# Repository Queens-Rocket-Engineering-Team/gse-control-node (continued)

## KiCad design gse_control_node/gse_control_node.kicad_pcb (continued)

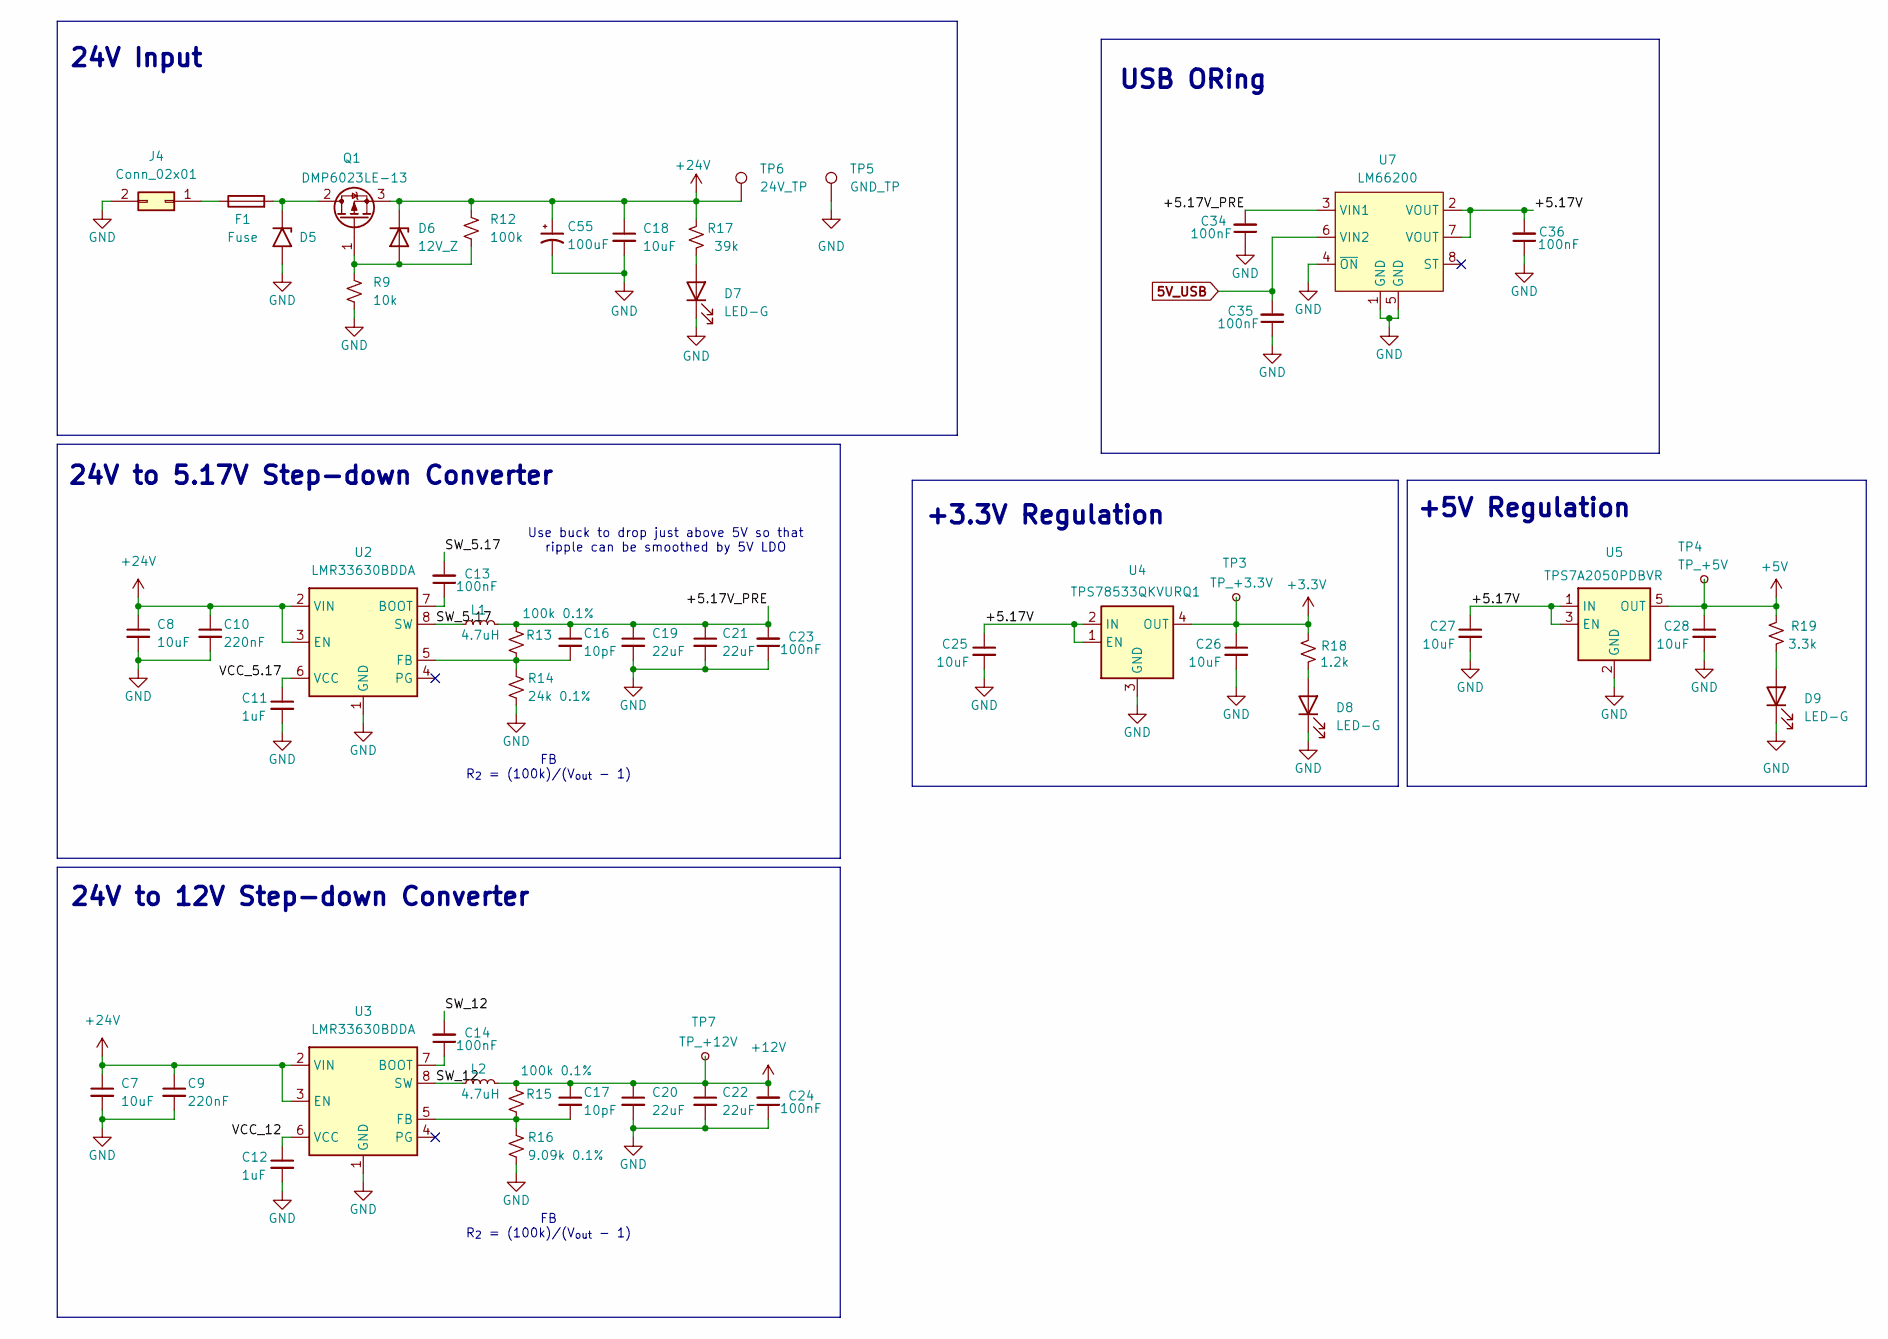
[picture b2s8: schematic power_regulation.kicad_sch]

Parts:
C7, C8, C18: 10uF; C_1206_3216Metric; LCSC C13585
C9, C10: 220nF; C_0805_2012Metric; LCSC C5378
C11, C12: 1uF; C_0603_1608Metric; LCSC C15849
C13, C14, C23, C24, C34, C35, C36: 100nF; C_0402_1005Metric; LCSC C307331
C16, C17: 10pF; C_0603_1608Metric; LCSC C1634
C19, C20, C21, C22: 22uF; C_0805_2012Metric; LCSC C45783
C25, C26, C27, C28: 10uF; C_0805_2012Metric; LCSC C15850
C55: 100uF; CP_Radial_D8.0mm_P5.00mm; MPN EEU-FR1H101B
D5: SMCJ26A-13-F; D_SMC; LCSC C135156
D6: 12V_Z; D_SOD-123; LCSC C500776
D7, D8, D9: LED-G; LED_0805_2012Metric; LCSC C2297
F1: Fuse; Fuseholder_Blade_Mini_Keystone_3568; LCSC N/A
J4: Conn_02x01; Molex_Mini-Fit_Jr_5566-02A_2x01_P4.20mm_Vertical; LCSC N/A
L1, L2: 4.7uH; L_Bourns_SRP7028A_7.3x6.6mm; LCSC C840529
Q1: DMP6023LE-13; SOT-223-3_TabPin2; LCSC C154901
R9: 10k; R_0603_1608Metric; LCSC C25804
R12: 100k; R_0603_1608Metric; LCSC C122538
R13, R15: 100k 0.1%; R_0603_1608Metric; LCSC C122538
R14: 24k 0.1%; R_0603_1608Metric; LCSC C326729
R16: 9.09k 0.1%; R_0603_1608Metric; LCSC C861611
R17: 39k; R_0603_1608Metric; LCSC C23153
R18: 1.2k; R_0603_1608Metric
R19: 3.3k; R_0603_1608Metric; LCSC C22978
TP3: TP_+3.3V; TestPoint_Pad_D1.0mm; LCSC N/A
TP4: TP_+5V; TestPoint_Pad_D1.0mm; LCSC N/A
TP5: GND_TP; TestPoint_Loop_D2.50mm_Drill1.0mm; LCSC N/A
TP6: 24V_TP; TestPoint_Loop_D2.50mm_Drill1.0mm; LCSC N/A
TP7: TP_+12V; TestPoint_Pad_D1.0mm; LCSC N/A
U2, U3: LMR33630BDDA; Texas_HSOP-8-1EP_3.9x4.9mm_P1.27mm_ThermalVias; LCSC C544370
U4: TPS78533QKVURQ1; TO-252-4; LCSC C3748131
U5: TPS7A2050PDBVR; SOT-23-5; LCSC C2864504
U7: LM66200; SOT-583-8; LCSC C3235556

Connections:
5V_USB: C35.2, U7.6 (VIN2); also elsewhere on the board
+3.3V: C26.1, R18.2, TP3.1 (1_1), U4.4 (OUT); also elsewhere on the board
+5V: C28.1, R19.2, TP4.1 (1_1), U5.5 (OUT); also elsewhere on the board
+12V: C17.1, C20.1, C22.1, C24.2, L2.2, R15.1, TP7.1 (1_1); also elsewhere on the board
+24V: C7.1, C8.1, C9.1, C10.1, C18.1, C55.1, D6.1 (K), Q1.3 (S), R12.1, R17.2, TP6.1 (1_1), U2.2 (VIN), U2.3 (EN), U3.2 (VIN), U3.3 (EN); also elsewhere on the board
/Power Regulation/+5.17V: C25.1, C27.1, C36.2, U4.1 (EN), U4.2 (IN), U5.1 (IN), U5.3 (EN), U7.2 (VOUT), U7.7 (VOUT)
/Power Regulation/+5.17V_PRE: C16.1, C19.1, C21.1, C23.2, C34.2, L1.2, R13.1, U7.3 (VIN1)
/Power Regulation/SW_5.17: C13.2, L1.1, U2.8 (SW)
/Power Regulation/SW_12: C14.2, L2.1, U3.8 (SW)
/Power Regulation/VCC_5.17: C11.1, U2.6 (VCC)
/Power Regulation/VCC_12: C12.1, U3.6 (VCC)
GND: C7.2, C8.2, C9.2, C10.2, C11.2, C12.2, C18.2, C19.2, C20.2, C21.2, C22.2, C23.1, C24.1, C25.2, C26.2, C27.2, C28.2, C34.1, C35.1, C36.1, C55.2, D5.2 (A2), D7.1 (K), D8.1 (K), D9.1 (K), J4.2, R9.2, R14.2, R16.2, TP5.1 (1_1), U2.1 (GND), U2.9 (GND), U3.1 (GND), U3.9 (GND), U4.3 (GND), U5.2 (GND), U7.1 (GND), U7.4 (~ON), U7.5 (GND); also elsewhere on the board
unnamed: D5.1 (A1), F1.2, Q1.2 (D)
unnamed: D6.2 (A), Q1.1 (G), R9.1, R12.2
unnamed: D7.2 (A), R17.1
unnamed: D8.2 (A), R18.1
unnamed: D9.2 (A), R19.1
unnamed: F1.1, J4.1
unnamed: C13.1, U2.7 (BOOT)
unnamed: C16.2, R13.2, R14.1, U2.5 (FB)
unnamed: C14.1, U3.7 (BOOT)
unnamed: C17.2, R15.2, R16.1, U3.5 (FB)

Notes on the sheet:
Use buck to drop just above 5V so that ripple can be smoothed by 5V LDO
24V Input
24V to 5.17V Step-down Converter
FB R_{2} = (100k)/(V_{out} - 1)
24V to 12V Step-down Converter
+3.3V Regulation
USB ORing
+5V Regulation

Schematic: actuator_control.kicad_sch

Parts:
D11, D15, D19, D23: SK44BL; D_SMB; LCSC C151740
J7, J15, J22, J26: Conn_01x02; Molex_Micro-Fit_3.0_43650-0215_1x02_P3.00mm_Vertical; LCSC N/A
Q2, Q7, Q13, Q17: BSS138; SOT-23-3; LCSC C82045
R24, R36, R58, R66: 100; R_0603_1608Metric
R25, R33, R57, R65: 100k; R_0603_1608Metric; LCSC C122538

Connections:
+24V: D11.1 (K), D15.1 (K), D19.1 (K), D23.1 (K), J7.1, J15.1, J22.1, J26.1; also elsewhere on the board
ACT1_CTL: R24.1, R25.1; also elsewhere on the board
ACT2_CTL: R33.1, R36.1; also elsewhere on the board
ACT3_CTL: R57.1, R58.1; also elsewhere on the board
ACT4_CTL: R65.1, R66.1; also elsewhere on the board
GND: Q2.2 (S), Q7.2 (S), Q13.2 (S), Q17.2 (S), R25.2, R33.2, R57.2, R65.2; also elsewhere on the board
unnamed: D11.2 (A), J7.2, Q2.3 (D)
unnamed: D15.2 (A), J15.2, Q7.3 (D)
unnamed: D19.2 (A), J22.2, Q13.3 (D)
unnamed: D23.2 (A), J26.2, Q17.3 (D)
unnamed: Q2.1 (G), R24.2
unnamed: Q7.1 (G), R36.2
unnamed: Q13.1 (G), R58.2
unnamed: Q17.1 (G), R66.2

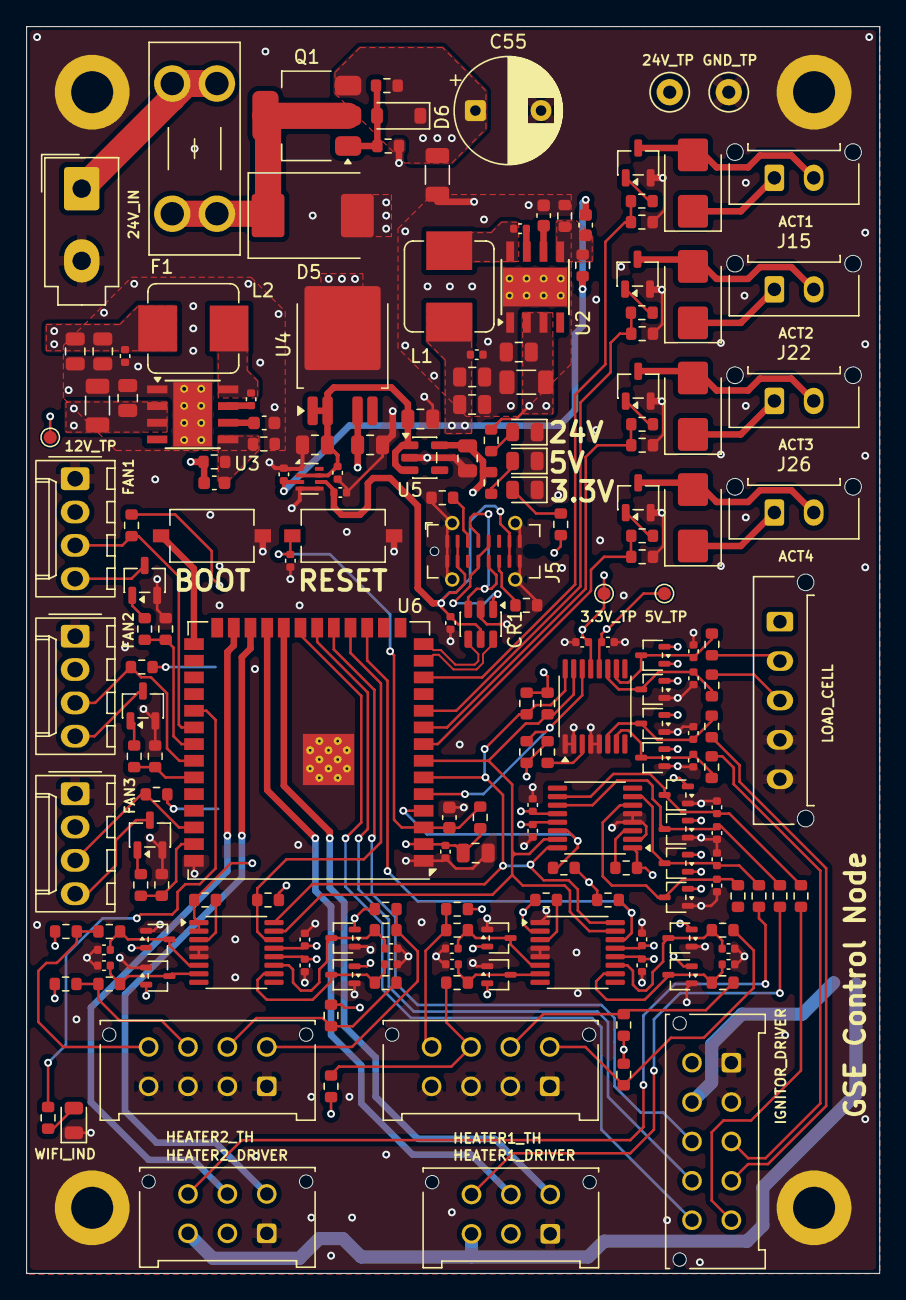
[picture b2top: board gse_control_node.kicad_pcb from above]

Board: 4 copper layers, 65.0 x 95.0 mm, 192 parts (0 on the bottom side), 104 nets.

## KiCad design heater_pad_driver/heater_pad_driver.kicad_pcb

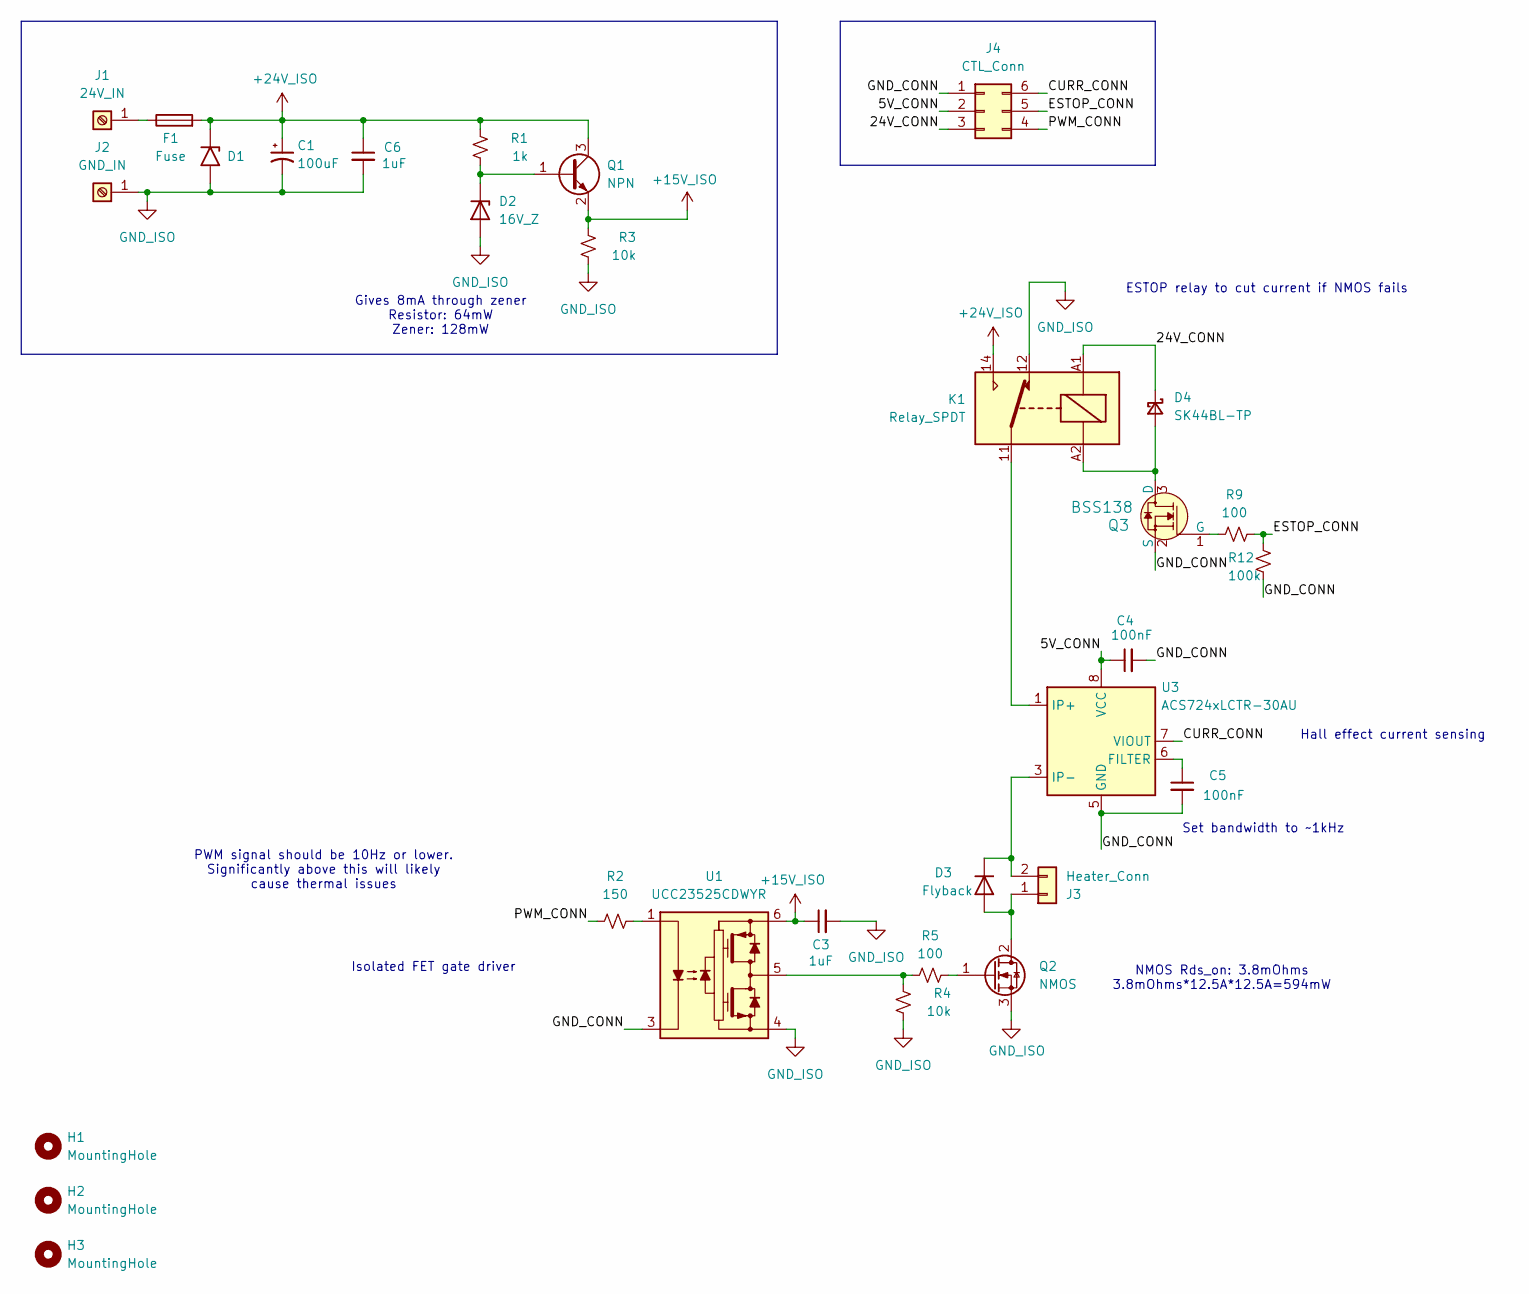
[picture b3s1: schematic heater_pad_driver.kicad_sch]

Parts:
C1: 100uF; CP_Radial_D8.0mm_P5.00mm; MPN EEU-FR1H101B
C3, C6: 1uF; C_0805_2012Metric_Pad1.18x1.45mm_HandSolder
C4, C5: 100nF; C_0805_2012Metric_Pad1.18x1.45mm_HandSolder
D1: SMCJ26A-13-F; D_SMC
D2: 16V_Z; D_SOD-123; MPN MMSZ5246BT1G
D3: Flyback; TO-220F-2_Vertical; MPN SDURK20Q60
D4: SK44BL-TP; D_SMB_Handsoldering; MPN SK44BL-TP
F1: Fuse; Fuseholder_Blade_Mini_Keystone_3568
H1, H2, H3: MountingHole; MountingHole_3.2mm_M3
J1: 24V_IN; AMT0440007DB0000G; MPN AMT0440007DB0000G
J2: GND_IN; AMT0440007DB0000G; MPN AMT0440007DB0000G
J3: Heater_Conn; AMASS_XT60PW-M_1x02_P7.20mm_Horizontal
J4: CTL_Conn; Molex_Micro-Fit_3.0_43045-0612_2x03_P3.00mm_Vertical
K1: Relay_SPDT; AZ576-1C
Q1: NPN; SOT-23_Handsoldering; MPN MMBTA06LT1G
Q2: NMOS; TO-252-2; MPN DMTH6004SK3Q-13
Q3: BSS138; SOT-23; MPN BSS138
R1: 1k; R_0805_2012Metric_Pad1.20x1.40mm_HandSolder
R2: 150; R_0805_2012Metric_Pad1.20x1.40mm_HandSolder
R3, R4: 10k; R_0805_2012Metric_Pad1.20x1.40mm_HandSolder
R5, R9: 100; R_0805_2012Metric_Pad1.20x1.40mm_HandSolder
R12: 100k; R_0805_2012Metric_Pad1.20x1.40mm_HandSolder
U1: UCC23525CDWYR; SSO-6_6.8x4.6mm_P1.27mm_Clearance8mm
U3: ACS724xLCTR-30AU; SOIC-8_3.9x4.9mm_P1.27mm; MPN ACS724LLCTR-30AU-T

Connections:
+15V_ISO: C3.1, Q1.2 (E), R3.2, U1.6 (VCC)
+24V_ISO: C1.1, C6.1, D1.1 (A1), F1.2, K1.14, Q1.3 (C), R1.2
/5V_CONN: C4.1, J4.2, U3.8 (VCC)
/24V_CONN: D4.1 (K), J4.3, K1.A1
/CURR_CONN: J4.6, U3.7 (VIOUT)
/ESTOP_CONN: J4.5, R9.2, R12.1
/GND_CONN: C4.2, C5.2, J4.1, Q3.2 (S), R12.2, U1.3 (C), U3.5 (GND)
/PWM_CONN: J4.4, R2.2
GND_ISO: C1.2, C3.2, C6.2, D1.2 (A2), D2.2 (A), J2.1 (Pin_1_1), K1.12, Q2.3 (S), R3.1, R4.1, U1.4 (VEE)
unnamed: D2.1 (K), Q1.1 (B), R1.1
unnamed: D3.2 (A), J3.1, Q2.2 (D)
unnamed: D3.1 (K), J3.2, U3.3 (IP-), U3.4 (IP-)
unnamed: D4.2 (A), K1.A2, Q3.3 (D)
unnamed: F1.1, J1.1 (Pin_1_1)
unnamed: K1.11, U3.1 (IP+), U3.2 (IP+)
unnamed: Q2.1 (G), R5.2
unnamed: Q3.1 (G), R9.1
unnamed: R2.1, U1.1 (A)
unnamed: R4.2, R5.1, U1.5 (VO)
unnamed: C5.1, U3.6 (FILTER)

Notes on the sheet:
Gives 8mA through zener Resistor: 64mW Zener: 128mW
Set bandwidth to ~1kHz
ESTOP relay to cut current if NMOS fails
Isolated FET gate driver
Hall effect current sensing
PWM signal should be 10Hz or lower. Significantly above this will likely cause thermal issues
NMOS Rds_on: 3.8mOhms 3.8mOhms*12.5A*12.5A=594mW

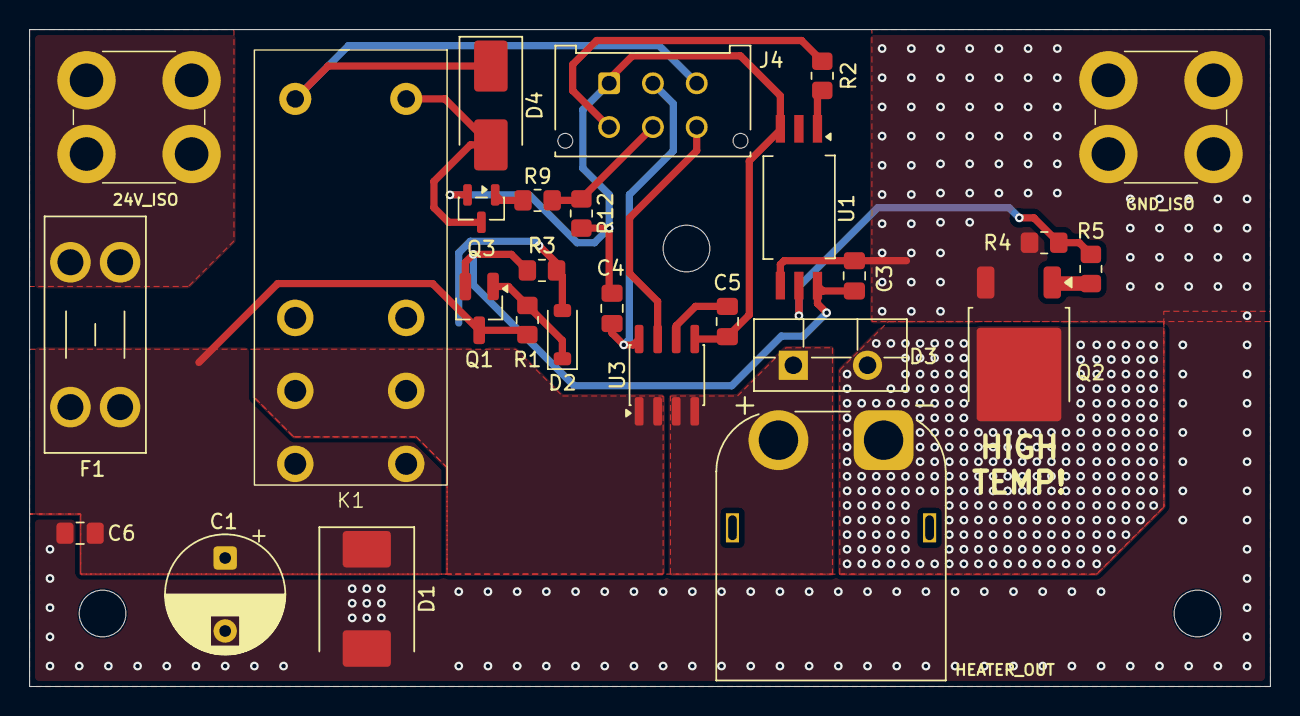
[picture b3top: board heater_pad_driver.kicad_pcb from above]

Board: 2 copper layers, 85.0 x 45.0 mm, 30 parts (0 on the bottom side), 20 nets.

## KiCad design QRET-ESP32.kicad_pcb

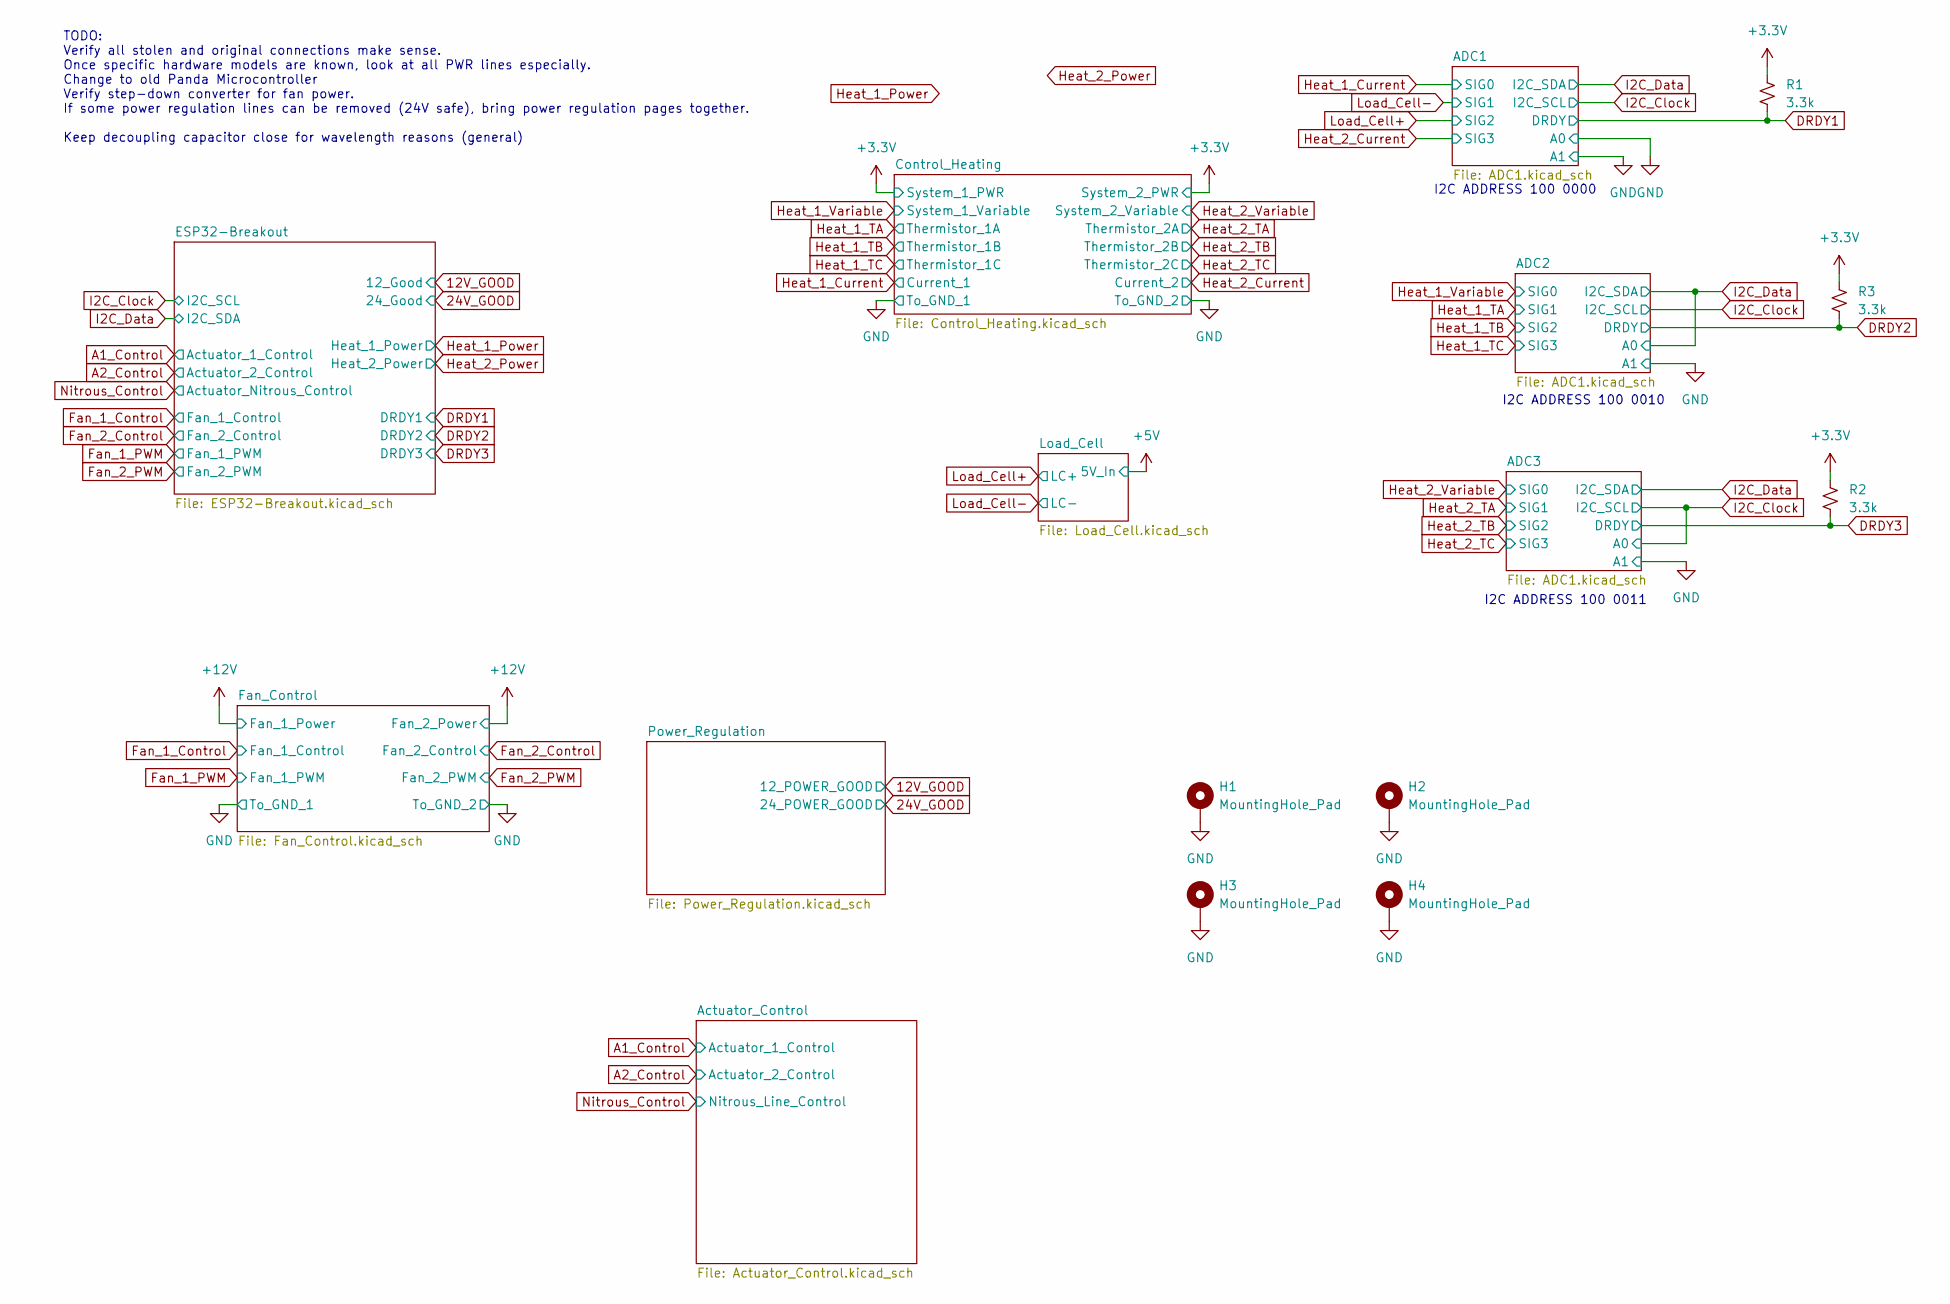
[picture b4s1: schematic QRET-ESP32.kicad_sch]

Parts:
H1, H2, H3, H4: MountingHole_Pad; MountingHole_3.2mm_M3_ISO7380_Pad
R1, R2, R3: 3.3k; R_0402_1005Metric

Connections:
DRDY1: R1.2; also elsewhere on the board
DRDY2: R3.2; also elsewhere on the board
DRDY3: R2.2; also elsewhere on the board

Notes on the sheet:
TODO: Verify all stolen and original connections make sense. Once specific hardware models are known, look at all PWR lines especially. Change to old Panda Microcontroller Verify step-down converter for fan power. If some power regulation lines can be removed (24V safe), bring power regulation page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
I2C ADDRESS 100 0000
I2C ADDRESS 100 0011
I2C ADDRESS 100 0010

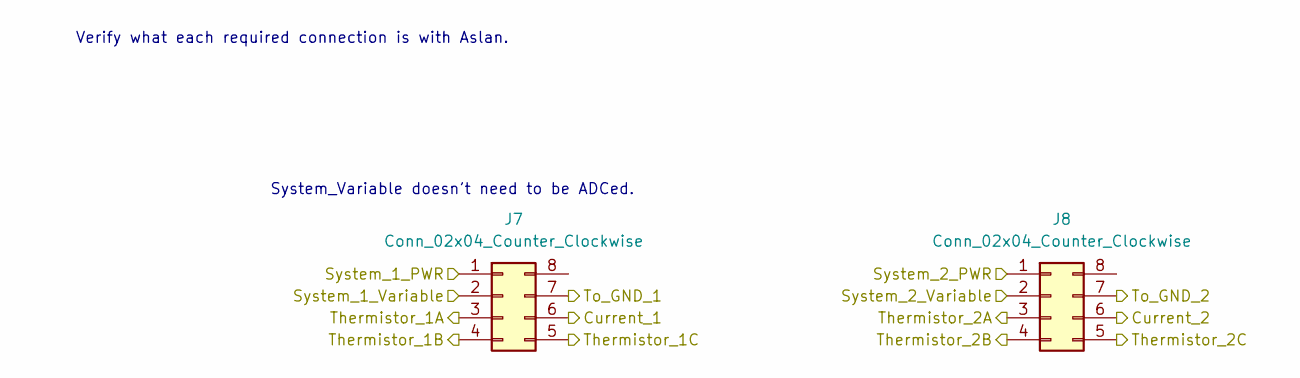
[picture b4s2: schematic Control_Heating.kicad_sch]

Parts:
J7, J8: Conn_02x04_Counter_Clockwise; JST_J2100_B08B-J21DK-GGXR_2x04_P2.50x4.00mm_Vertical

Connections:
Heat_1_Current: J7.6; also elsewhere on the board
Heat_1_TA: J7.3; also elsewhere on the board
Heat_1_TB: J7.4; also elsewhere on the board
Heat_1_TC: J7.5; also elsewhere on the board
Heat_1_Variable: J7.2; also elsewhere on the board
Heat_2_Current: J8.6; also elsewhere on the board
Heat_2_TA: J8.3; also elsewhere on the board
Heat_2_TB: J8.4; also elsewhere on the board
Heat_2_TC: J8.5; also elsewhere on the board
Heat_2_Variable: J8.2; also elsewhere on the board

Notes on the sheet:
Verify what each required connection is with Aslan.
System_Variable doesn't need to be ADCed.

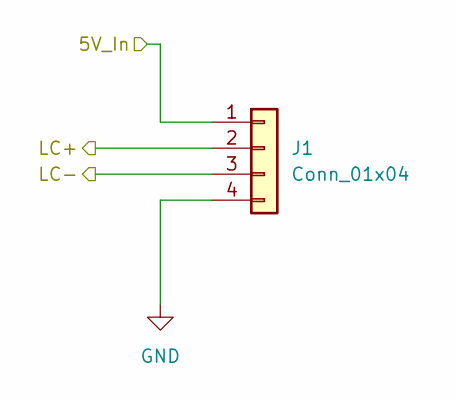
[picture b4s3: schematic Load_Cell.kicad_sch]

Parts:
J1: Conn_01x04; JST_EH_B4B-EH-A_1x04_P2.50mm_Vertical

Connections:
+5V: J1.1; also elsewhere on the board
Load_Cell+: J1.2; also elsewhere on the board
Load_Cell-: J1.3; also elsewhere on the board

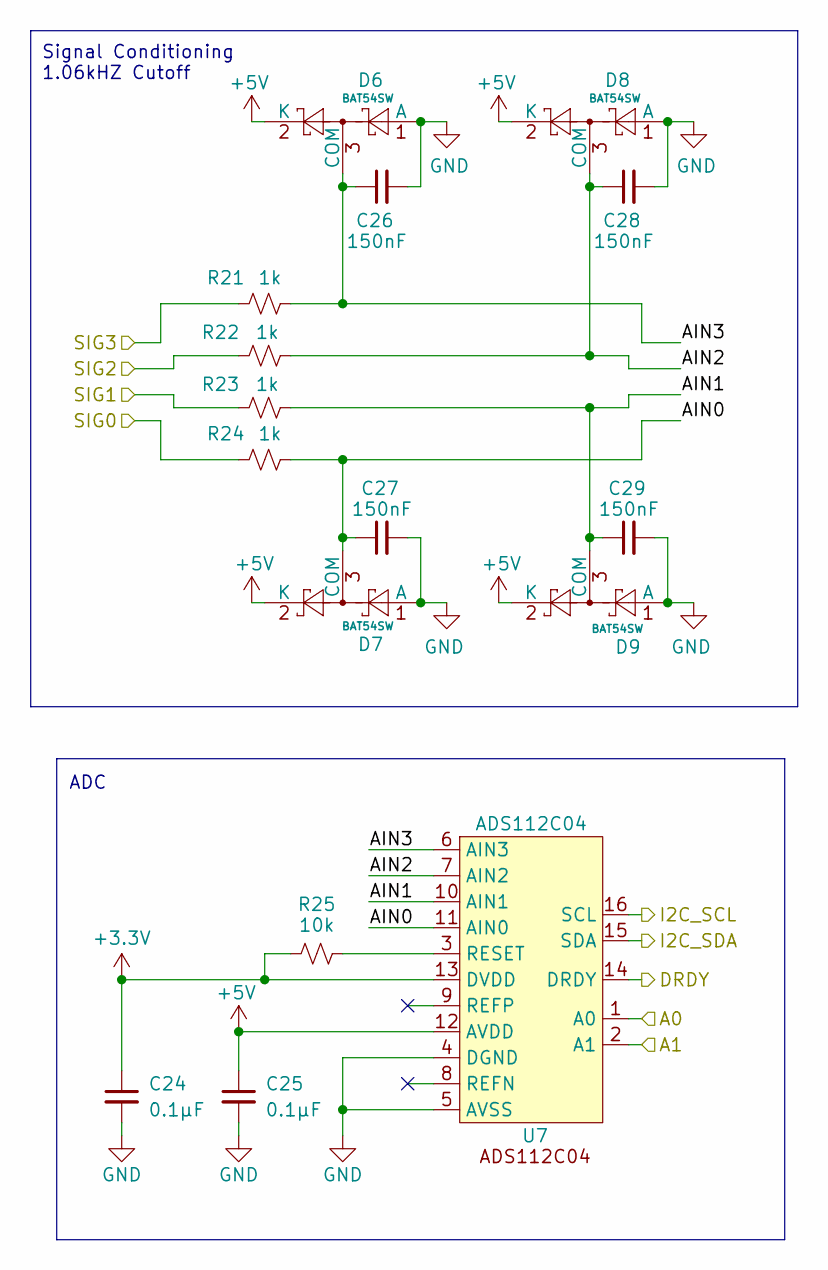
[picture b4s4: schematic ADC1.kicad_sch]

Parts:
C24, C25: 0.1μF; C_0402_1005Metric; MPN CL05B104KO5NNNC; LCSC C307331
C26, C27, C28, C29: 150nF; C_0402_1005Metric; LCSC C576725
D6, D7, D8, D9: BAT54SW; SOT-323_SC-70; LCSC C83575
R21, R22, R23, R24: 1k; R_0402_1005Metric
R25: 10k; R_0402_1005Metric; MPN 0402WGJ0103TCE; LCSC C25531
U7: ADS112C04; TSSOP-16_4.4x5mm_P0.65mm; MPN ADS112C04IPWR; LCSC C701615

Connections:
+5V: C25.1, D6.2 (K), D7.2 (K), D8.2 (K), D9.2 (K), U7.12 (AVDD); also elsewhere on the board
/ADC1/AIN0: C27.1, D7.3 (COM), R24.2, U7.11 (AIN0)
/ADC1/AIN1: C29.1, D9.3 (COM), R23.2, U7.10 (AIN1)
/ADC1/AIN2: C28.1, D8.3 (COM), R22.2, U7.7 (AIN2)
/ADC1/AIN3: C26.1, D6.3 (COM), R21.2, U7.6 (AIN3)
DRDY1: U7.14 (DRDY); also elsewhere on the board
Heat_1_Current: R24.1; also elsewhere on the board
Heat_2_Current: R21.1; also elsewhere on the board
I2C_Clock: U7.16 (SCL); also elsewhere on the board
I2C_Data: U7.15 (SDA); also elsewhere on the board
Load_Cell+: R22.1; also elsewhere on the board
Load_Cell-: R23.1; also elsewhere on the board
unnamed: R25.2, U7.3 (RESET)

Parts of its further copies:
C30, C31, C36, C37: 0.1μF; C_0402_1005Metric; MPN CL05B104KO5NNNC; LCSC C307331
C32, C33, C34, C35, C38, C39, C40, C41: 150nF; C_0402_1005Metric; LCSC C576725
D10, D11, D12, D13, D14, D15, D16, D17: BAT54SW; SOT-323_SC-70; LCSC C83575
R26, R27, R28, R29, R31, R32, R33, R34: 1k; R_0402_1005Metric
R30, R35: 10k; R_0402_1005Metric; MPN 0402WGJ0103TCE; LCSC C25531
U8, U9: ADS112C04; TSSOP-16_4.4x5mm_P0.65mm; MPN ADS112C04IPWR; LCSC C701615

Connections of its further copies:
+5V: C31.1, C37.1, D10.2 (K), D11.2 (K), D12.2 (K), D13.2 (K), D14.2 (K), D15.2 (K), D16.2 (K), D17.2 (K), U8.12 (AVDD), U9.12 (AVDD); also elsewhere on the board
/ADC2/AIN0: C33.1, D11.3 (COM), R29.2, U8.11 (AIN0)
/ADC2/AIN1: C35.1, D13.3 (COM), R28.2, U8.10 (AIN1)
/ADC2/AIN2: C34.1, D12.3 (COM), R27.2, U8.7 (AIN2)
/ADC2/AIN3: C32.1, D10.3 (COM), R26.2, U8.6 (AIN3)
/ADC3/AIN0: C39.1, D15.3 (COM), R34.2, U9.11 (AIN0)
/ADC3/AIN1: C41.1, D17.3 (COM), R33.2, U9.10 (AIN1)
/ADC3/AIN2: C40.1, D16.3 (COM), R32.2, U9.7 (AIN2)
/ADC3/AIN3: C38.1, D14.3 (COM), R31.2, U9.6 (AIN3)
DRDY2: U8.14 (DRDY); also elsewhere on the board
DRDY3: U9.14 (DRDY); also elsewhere on the board
Heat_1_TA: R28.1; also elsewhere on the board
Heat_1_TB: R27.1; also elsewhere on the board
Heat_1_TC: R26.1; also elsewhere on the board
Heat_1_Variable: R29.1; also elsewhere on the board
Heat_2_TA: R33.1; also elsewhere on the board
Heat_2_TB: R32.1; also elsewhere on the board
Heat_2_TC: R31.1; also elsewhere on the board
Heat_2_Variable: R34.1; also elsewhere on the board
I2C_Clock: U8.16 (SCL), U9.1 (A0), U9.16 (SCL); also elsewhere on the board
I2C_Data: U8.1 (A0), U8.15 (SDA), U9.15 (SDA); also elsewhere on the board
unnamed: R30.2, U8.3 (RESET)
unnamed: R35.2, U9.3 (RESET)

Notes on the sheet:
ADC
Signal Conditioning 1.06kHZ Cutoff

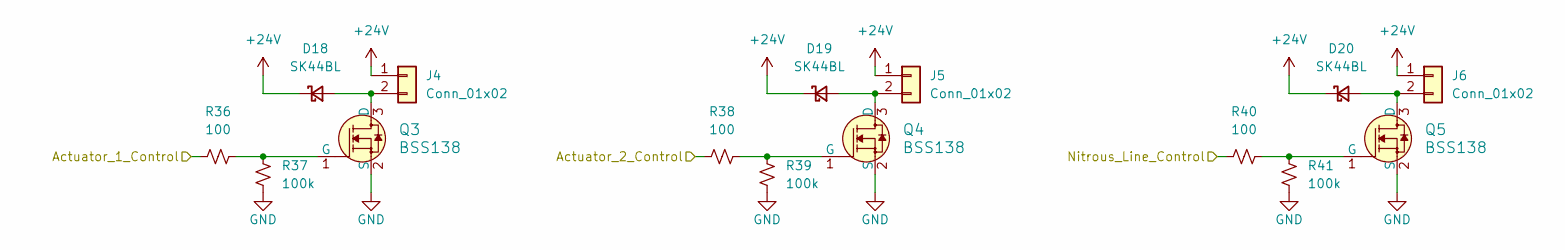
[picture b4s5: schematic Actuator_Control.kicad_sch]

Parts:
D18, D19, D20: SK44BL; D_SMB; MPN SK44BL-TP; LCSC C151740
J4, J5, J6: Conn_01x02; JST_EH_B2B-EH-A_1x02_P2.50mm_Vertical
Q3, Q4, Q5: BSS138; SOT-23-3; MPN BSS138; LCSC C8490
R36, R38, R40: 100; R_0402_1005Metric; MPN 0402WGF1000TCE; LCSC C25076
R37, R39, R41: 100k; R_0603_1608Metric; MPN 0402WGJ0104TCE; LCSC C25530

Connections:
+24V: D18.1 (K), D19.1 (K), D20.1 (K), J4.1, J5.1, J6.1; also elsewhere on the board
A1_Control: R36.1; also elsewhere on the board
A2_Control: R38.1; also elsewhere on the board
unnamed: D18.2 (A), J4.2, Q3.3 (D)
unnamed: D19.2 (A), J5.2, Q4.3 (D)
unnamed: D20.2 (A), J6.2, Q5.3 (D)
unnamed: Q3.1 (G), R36.2, R37.1
unnamed: Q4.1 (G), R38.2, R39.1
unnamed: Q5.1 (G), R40.2, R41.1
Nitrous_Control: R40.1; also elsewhere on the board

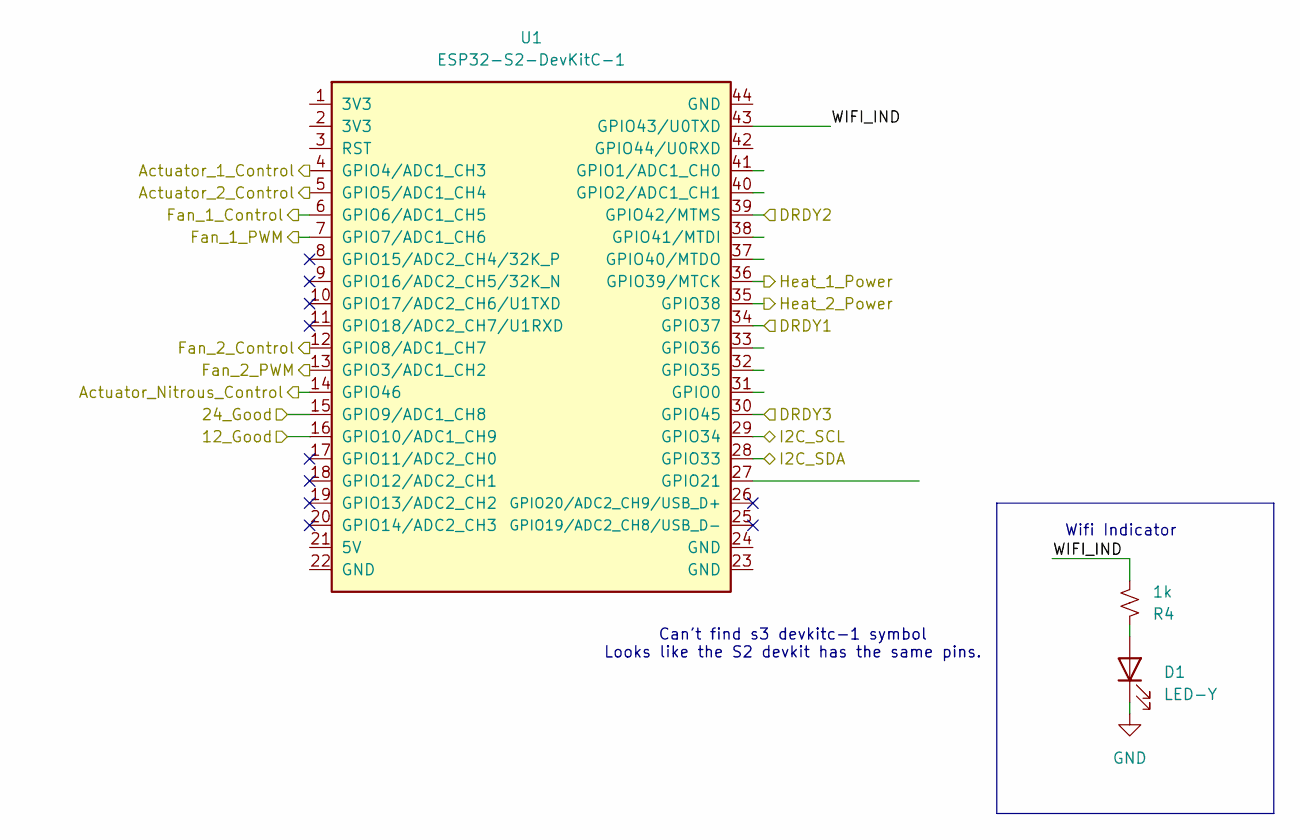
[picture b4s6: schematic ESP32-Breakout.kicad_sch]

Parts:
D1: LED-Y; LED_0805_2012Metric; LCSC C2296
R4: 1k; R_0402_1005Metric
U1: ESP32-S2-DevKitC-1

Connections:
12V_GOOD: U1.16 (GPIO10/ADC1_CH9); also elsewhere on the board
24V_GOOD: U1.15 (GPIO9/ADC1_CH8); also elsewhere on the board
/ESP32-Breakout/WIFI_IND: R4.2, U1.43 (GPIO43/U0TXD)
A1_Control: U1.4 (GPIO4/ADC1_CH3); also elsewhere on the board
A2_Control: U1.5 (GPIO5/ADC1_CH4); also elsewhere on the board
DRDY1: U1.34 (GPIO37); also elsewhere on the board
DRDY2: U1.39 (GPIO42/MTMS); also elsewhere on the board
DRDY3: U1.30 (GPIO45); also elsewhere on the board
Fan_1_Control: U1.6 (GPIO6/ADC1_CH5); also elsewhere on the board
Fan_1_PWM: U1.7 (GPIO7/ADC1_CH6); also elsewhere on the board
Fan_2_Control: U1.12 (GPIO8/ADC1_CH7); also elsewhere on the board
Fan_2_PWM: U1.13 (GPIO3/ADC1_CH2); also elsewhere on the board
Heat_1_Power: U1.36 (GPIO39/MTCK)
Heat_2_Power: U1.35 (GPIO38)
I2C_Clock: U1.29 (GPIO34); also elsewhere on the board
I2C_Data: U1.28 (GPIO33); also elsewhere on the board
unnamed: D1.2 (A), R4.1
Nitrous_Control: U1.14 (GPIO46); also elsewhere on the board

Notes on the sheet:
Can't find s3 devkitc-1 symbol Looks like the S2 devkit has the same pins.
Wifi Indicator

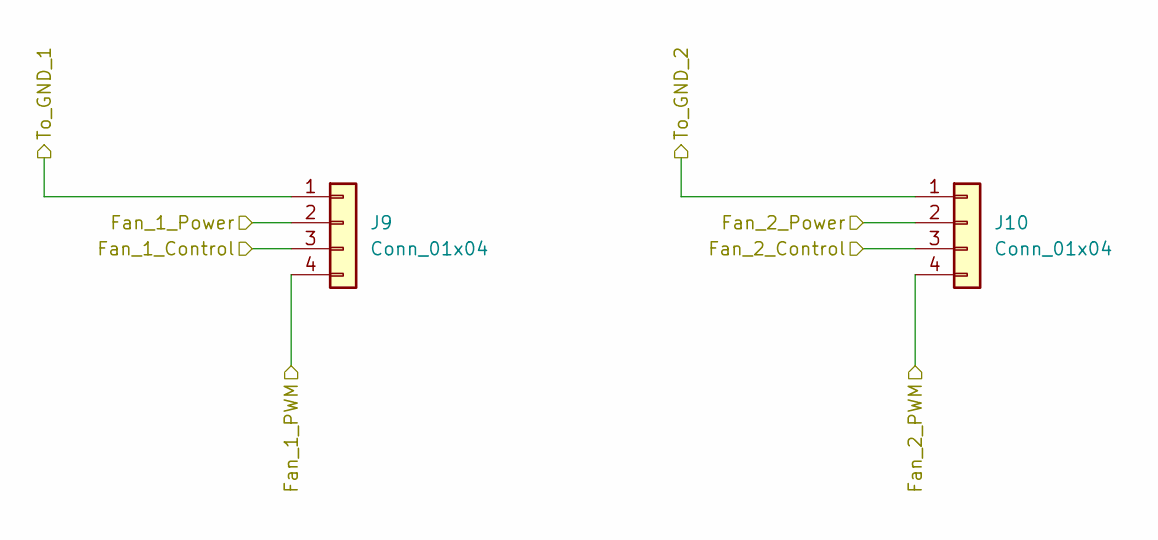
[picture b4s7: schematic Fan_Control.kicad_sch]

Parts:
J9, J10: Conn_01x04; JST_EH_B4B-EH-A_1x04_P2.50mm_Vertical

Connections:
+12V: J9.2, J10.2; also elsewhere on the board
Fan_1_Control: J9.3; also elsewhere on the board
Fan_1_PWM: J9.4; also elsewhere on the board
Fan_2_Control: J10.3; also elsewhere on the board
Fan_2_PWM: J10.4; also elsewhere on the board
